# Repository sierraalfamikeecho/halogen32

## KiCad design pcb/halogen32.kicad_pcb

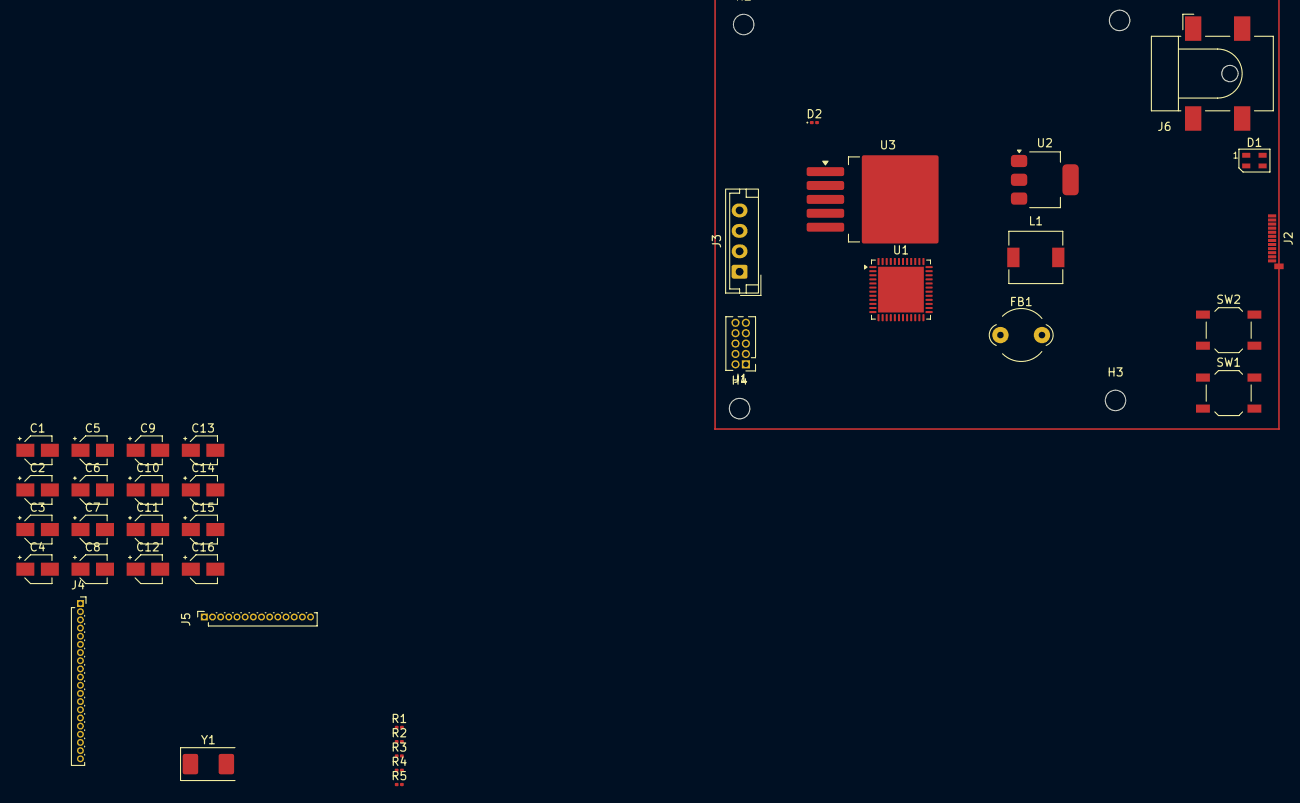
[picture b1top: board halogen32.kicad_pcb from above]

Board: 2 copper layers, 41 parts (0 on the bottom side), 49 nets, no tracks yet.

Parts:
C1, C2, C3, C4: 100n; CP_Elec_3x5.3
C5: 10u; CP_Elec_3x5.3
C6: 10n; CP_Elec_3x5.3
C7, C8: 1u; CP_Elec_3x5.3
C9, C13: 22u; CP_Elec_3x5.3
C10, C11: 10p; CP_Elec_3x5.3
C12: 1000u; CP_Elec_3x5.3
C14: 2.2u; CP_Elec_3x5.3
C15: 2200u; CP_Elec_3x5.3
C16: 100u; CP_Elec_3x5.3
D1: SK6805; LED_SK6805_PLCC4_2.4x2.7mm_P1.3mm
D2: D; D_0201_0603Metric
FB1: 120R; LairdTech_28C0236-0JW-10
H1, H2, H3, H4: MountingHole; MountingHole_2.5mm
J1: Conn_ARM_JTAG_SWD_10; PinHeader_2x05_P1.27mm_Vertical
J2: USB_C_Receptacle_USB2.0_16P; USB_C_Plug_Molex_105444
J3: Conn_01x04_Pin; JST_EH_B4B-EH-A_1x04_P2.50mm_Vertical
J4: Conn_01x20_Socket; PinSocket_1x20_P1.00mm_Vertical
J5: Conn_01x14_Socket; PinSocket_1x14_P1.00mm_Vertical
J6: Barrel_Jack; BarrelJack_CLIFF_FC681465S_SMT_Horizontal
L1: 68u; L_6.3x6.3_H3
R1, R3, R4, R5: 5.1k; R_0201_0603Metric
R2: 500; R_0201_0603Metric
SW1, SW2: SW_SPDT; SW_SPST_TL3342
U1: STM32F411CEUx; QFN-48-1EP_7x7mm_P0.5mm_EP5.6x5.6mm
U2: AMS1117-3.3; SOT-223-3_TabPin2
U3: LM2576HVS-5; TO-263-5_TabPin3
Y1: 16MHz; Crystal_SMD_0603-2Pin_6.0x3.5mm

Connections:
+3.3V: C1.1, C2.1, C3.1, C4.1, C5.1, C6.1, C7.1, C8.1, C13.1, FB1.1, FB1.2, J1.1 (VTref), J3.2, J5.11, U1.1 (VBAT), U1.9 (VDDA), U1.24 (VDD), U1.36 (VDD), U1.48 (VDD), U2.2 (VO)
+5V: C9.2, C12.1, C15.2, D1.4 (VDD), D2.2 (A), J2.A4 (VBUS), J2.A9 (VBUS), J2.B4 (VBUS), J2.B9 (VBUS), J5.10, J5.13, U2.3 (VI), U3.3 (GND), U3.5 (~ON/OFF)
/AREF: J4.3, U1.30 (PA9)
/BOOT: J5.14, R1.2, U1.44 (BOOT0)
/HSE-IN: C10.1, U1.5 (PH0), Y1.1
/HSE-OUT: C11.1, U1.6 (PH1)
/I2C1_SCL: J3.4, U1.42 (PB6)
/I2C1_SDA: J3.3, U1.43 (PB7)
/NRST: J1.10 (~RESET), J5.12, R3.2, U1.7 (NRST)
/PA0: J5.6, U1.10 (PA0)
/PA1: J5.5, U1.11 (PA1)
/PA2: J5.4, U1.12 (PA2)
/PA3: J5.3, U1.13 (PA3)
/PA4: J5.2, U1.14 (PA4)
/PA5: J5.1, U1.15 (PA5)
/PA6: J4.1, U1.16 (PA6)
/PA8: J4.11, U1.29 (PA8)
/PB0: J4.20, U1.18 (PB0)
/PB1: J4.19, U1.19 (PB1)
/PB2: J4.18, U1.20 (PB2)
/PB3: J4.17, U1.39 (PB3)
/PB4: J4.16, U1.40 (PB4)
/PB5: J4.15, U1.41 (PB5)
/PB8: J4.14, U1.45 (PB8)
/PB9: J4.13, U1.46 (PB9)
/PB10: J4.12, U1.21 (PB10)
/PB12: J4.10, U1.25 (PB12)
/PB13: J4.9, U1.26 (PB13)
/PB14: J4.8, U1.27 (PB14)
/PB15: J4.7, U1.28 (PB15)
/PC13: J4.6, U1.2 (PC13)
/PC14: J4.5, U1.3 (PC14)
/PC15: J4.2, U1.4 (PC15)
/STATUS_DIN: R2.1, U1.38 (PA15)
/SWCLK: J1.4 (SWCLK/TCK), U1.37 (PA14)
/SWDIO: J1.2 (SWDIO/TMS), U1.34 (PA13)
/SWO: J1.6 (SWO/TDO), U1.31 (PA10)
/USB_D+: J2.A6 (D+), U1.33 (PA12)
/USB_D-: J2.A7 (D-), U1.32 (PA11)
GND: C1.2, C2.2, C3.2, C4.2, C5.2, C6.2, C7.2, C8.2, C9.1, C10.2, C11.2, C12.2, C13.2, C14.2, C16.2, D1.2 (VSS), J1.3 (GND), J1.5 (GND), J1.9 (GNDDetect), J2.A1 (GND), J2.A12 (GND), J2.B1 (GND), J2.B12 (GND), J2.S1 (SHIELD), J3.1, J4.4, J5.8, J5.9, J6.2, L1.2, R4.2, R5.2, SW1.1 (A), SW2.1 (A), U1.8 (VSSA), U1.23 (VSS), U1.35 (VSS), U1.47 (VSS), U1.49 (VSS), U2.1 (GND), Y1.2
unnamed: D1.3 (DIN), R2.2
unnamed: D2.1 (K), L1.1, U3.2 (OUT)
unnamed: J2.A5 (CC1), R4.1
unnamed: J2.B5 (CC2), R5.1
unnamed: R1.1, SW1.2 (B)
unnamed: R3.1, SW2.2 (B)
unnamed: C14.1, U1.22 (VCAP1)
unnamed: C15.1, U3.4 (FB)
unnamed: C16.1, J6.1, U3.1 (VIN)

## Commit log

2026-01-27 Started work on PCB layout after resolving git issues.
2026-01-28 Added `shell.nix` including zephrRTOS west and pyspice libs.
2026-02-28 Moving schematic to Arduino Uno R4 form factor.
2026-02-28 Added IOREF pin and worked on shell.nix
2026-03-01 Added DC jack and buck converter
2026-03-01 Worked on footprints, just need to add SWD header, boot and reset switches, and Crystal footprints.
2026-03-04 Assigned footprints and imported footprints into pcb layout.
2026-03-04 Began work on rough layout.
2026-03-04 Added Makefile
